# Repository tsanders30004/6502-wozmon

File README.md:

# 6502 PCB Computer

## INTRODUCTION
- I was in highschool in the eighties when the *home computer revolution* introduced the world to computers running the MOS6502 and Z80 microprocessors.
- My first computer was an Atari 400 which used a 6502.
- When I added two numbers together in BASIC for the first time on that computer, I was hooked.   To this day, I am fascinated with computers.
- I couldn't help feeling nostalgic when I stumbled upon Ben Eater's excellent https://eater.net/6502 webpage, in which he describes how to build a 6502 computer on a breadboard.
- I quickly found out how difficult working with breadboards can be RE: unreliable connections, etc.  One loose wire was all it took to make the computer unusable.
- I therefore abandoned the breadboard altogether and instead decided to build a PCB.
- I had no idea how to do this; I could not even solder.  But I figured all of that out, and eventually I had a PCB that can run *HELLO WORLD* and *WOZMON*.
- This repository has all of the files necessary to build that PCB.

## PCB DESCRIPTION

|General Information||
|-|-|
|Microprocessor|WDC 65c02|
|I/O|65c22|
|UART|65c51|
|Clock|1MHz|
|ROM|32KB|
|RAM|32KB|
|Display|40x2 character LCD|
|Baud Rate|19200 8N1|

The upper left corner of the PCB has ports for +5V (barrel connector) and an RS-232 nine-pin serial cable.  
PWR and CLK LED's will illuminate when power and a clock signal (from the onboard 1MHz clock) are present, respectively.
The PCB can be reset via the RESET button directly below the RS-232 port.  The RESET LED will illuminate when the RESET button is pressed.

A column of output header pins is positioned immediately to the left of the LCD.  These output pins were primarily used for testing.  The top four pins are for GND.  (I used then when connecting the ground lead of an oscilloscope to the PCB.)  The bottom four pins are TxD, MAX232 pin 12, RESET*, and the CLOCK signal.  You can leave these pins unconnected if you don't want to use them.

## SOFTWARE 

|Filename|Description|
|-|-|
|software/hello/hello.s|'HELLO WORLD 6502' Assembly Code|
|software/hello/hello.out|'HELLO WORLD 6502' ROM file
|software/wozmon/wozmin.s|WOZMON Assembly Code|
|software/wozmon/wozmin.bin|WOZMON ROM file|

The computer *does not run the version of Microsoft BASIC* that Ben describes on his channel.  I have not figured (yet?) why that is so.  But it does run an alternate version of BASIC I found on Github.  See https://github.com/Fifty1Ford/BeEhBasic for more information.

## KICAD FILES

I used KiCad 6 to design the PCB.  
|Filename|Description|
|-|-|
|6502_wozmon.kicad_pro|KiCad 6 Project File|
|6502_wozmon.kicad_sch|KiCad 6 Schematic|
|6502_wozmon.kicad_pcb|KiCad 6 PCB File|
|6502_wozmon.csv|Bill of Materials|
|barrel_jack.pdf|Barrel Jack Power Connector|
|schematic.pdf|Schematic|
|photos/*.png|Photos|
|gerber/*|Gerber Files|

## CLOSING COMMENTS
- I am a hobbyist.  There are no doubt many ways to improve this design.  Feel free to do so! 
- I use a ZIF socket for the ROM chip to make it easier to remove.

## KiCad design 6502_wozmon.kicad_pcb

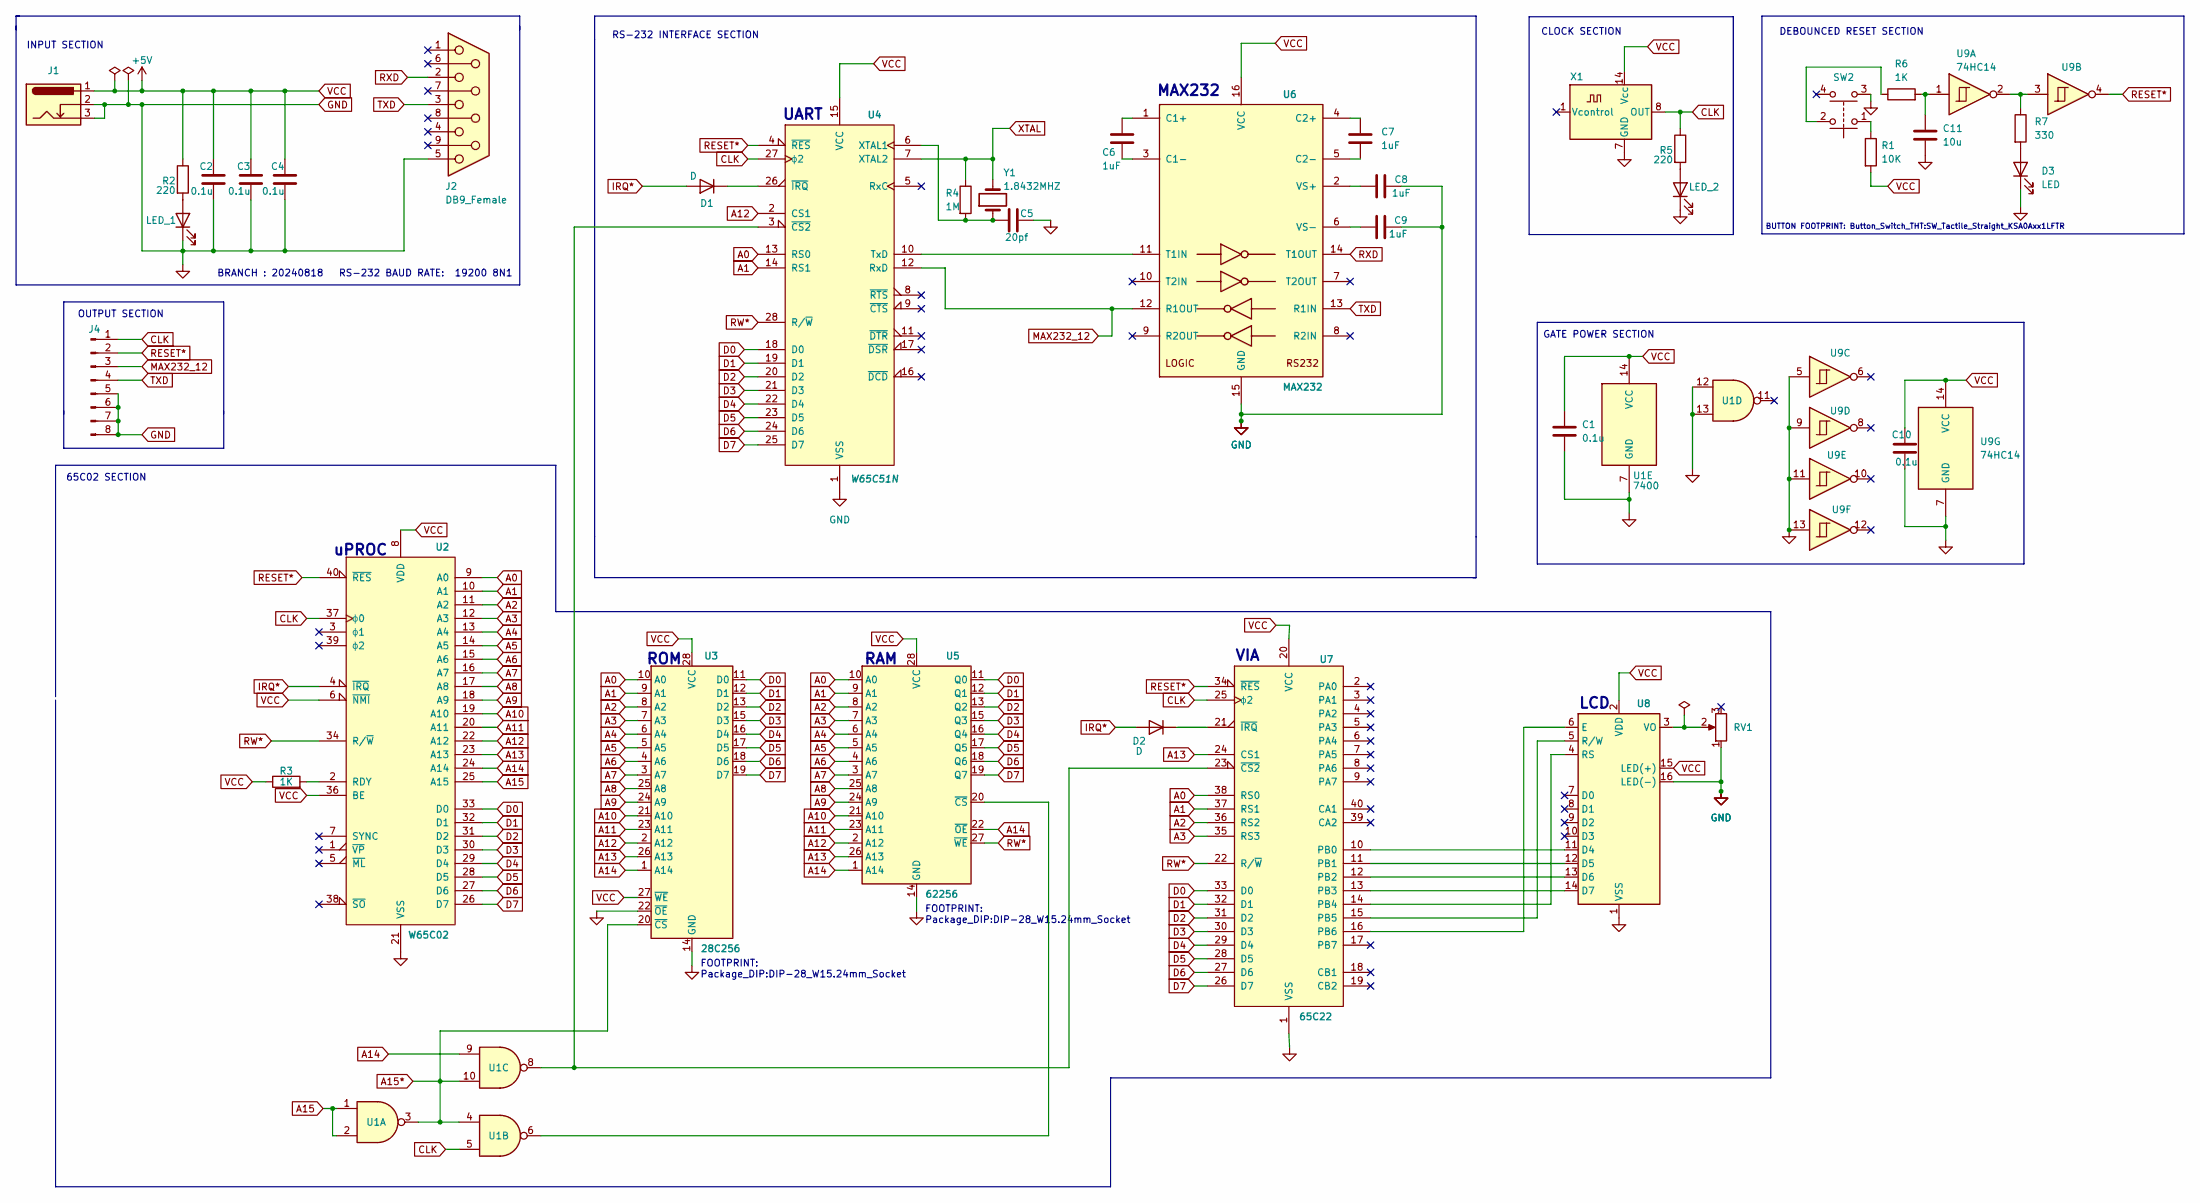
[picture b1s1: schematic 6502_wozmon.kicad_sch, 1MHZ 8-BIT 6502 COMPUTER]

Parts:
C1, C2, C3, C4, C10: 0.1u; C_Disc_D5.0mm_W2.5mm_P5.00mm
C5: 20pf; C_Disc_D5.0mm_W2.5mm_P5.00mm
C6, C7, C8, C9: 1uF; C_Disc_D5.0mm_W2.5mm_P5.00mm
C11: 10u; C_Disc_D5.0mm_W2.5mm_P5.00mm
D1, D2: D; D_A-405_P10.16mm_Horizontal
D3: LED; LED_D5.0mm
J1: Barrel_Jack_Switch_Pin3Ring; BarrelJack_Horizontal
J2: DB9_Female; DSUB-9_Female_Horizontal_P2.77x2.84mm_EdgePinOffset9.90mm_H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
J4: Conn_01x08_Male; PinHeader_1x08_P2.54mm_Vertical
LED_1, LED_2: LED; LED_D5.0mm
R1: 10K; R_Axial_DIN0207_L6.3mm_D2.5mm_P10.16mm_Horizontal
R2, R5: 220; R_Axial_DIN0207_L6.3mm_D2.5mm_P10.16mm_Horizontal
R3, R6: 1K; R_Axial_DIN0207_L6.3mm_D2.5mm_P10.16mm_Horizontal
R4: 1M; R_Axial_DIN0207_L6.3mm_D2.5mm_P10.16mm_Horizontal
R7: 330; R_Axial_DIN0207_L6.3mm_D2.5mm_P10.16mm_Horizontal
RV1: R_Potentiometer; Potentiometer_Bourns_3266Y_Vertical
SW2: SW_Push_Dual; SW_Tactile_Straight_KSA0Axx1LFTR
U1: 7400; DIP-14_W7.62mm_Socket
U2: W65C02; DIP-40_W15.24mm_Socket
U3: 28C256; DIP-28_W15.24mm_Socket
U4: W65C51N; DIP-28_W15.24mm_Socket
U5: 62256; DIP_Socket-28_W11.9_W12.7_W15.24_W17.78_W18.5_3M_228-1277-0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
U6: MAX232; DIP-16_W7.62mm_Socket
U7: 65C22; DIP-40_W15.24mm_Socket
U8: WC1602A
U9: 74HC14; DIP-14_W7.62mm_Socket
X1: GTXO-S14V; Oscillator_DIP-14
Y1: 1.8432MHZ; Crystal_HC18-U_Vertical

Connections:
A0: U2.9 (A0), U3.10 (A0), U4.13 (RS0), U5.10 (A0), U7.38 (RS0)
A1: U2.10 (A1), U3.9 (A1), U4.14 (RS1), U5.9 (A1), U7.37 (RS1)
A2: U2.11 (A2), U3.8 (A2), U5.8 (A2), U7.36 (RS2)
A3: U2.12 (A3), U3.7 (A3), U5.7 (A3), U7.35 (RS3)
A4: U2.13 (A4), U3.6 (A4), U5.6 (A4)
A5: U2.14 (A5), U3.5 (A5), U5.5 (A5)
A6: U2.15 (A6), U3.4 (A6), U5.4 (A6)
A7: U2.16 (A7), U3.3 (A7), U5.3 (A7)
A8: U2.17 (A8), U3.25 (A8), U5.25 (A8)
A9: U2.18 (A9), U3.24 (A9), U5.24 (A9)
A10: U2.19 (A10), U3.21 (A10), U5.21 (A10)
A11: U2.20 (A11), U3.23 (A11), U5.23 (A11)
A12: U2.22 (A12), U3.2 (A12), U4.2 (CS1), U5.2 (A12)
A13: U2.23 (A13), U3.26 (A13), U5.26 (A13), U7.24 (CS1)
A14: U1.9, U2.24 (A14), U3.1 (A14), U5.1 (A14), U5.22 (~OE)
A15: U1.1, U1.2, U2.25 (A15)
A15*: U1.3, U1.4, U1.10, U3.20 (~CS)
CLK: J4.1, R5.1, U1.5, U2.37 (ϕ0), U4.27 (ϕ2), U7.25 (ϕ2), X1.8 (OUT)
D0: U2.33 (D0), U3.11 (D0), U4.18 (D0), U5.11 (Q0), U7.33 (D0)
D1: U2.32 (D1), U3.12 (D1), U4.19 (D1), U5.12 (Q1), U7.32 (D1)
D2: U2.31 (D2), U3.13 (D2), U4.20 (D2), U5.13 (Q2), U7.31 (D2)
D3: U2.30 (D3), U3.15 (D3), U4.21 (D3), U5.15 (Q3), U7.30 (D3)
D4: U2.29 (D4), U3.16 (D4), U4.22 (D4), U5.16 (Q4), U7.29 (D4)
D5: U2.28 (D5), U3.17 (D5), U4.23 (D5), U5.17 (Q5), U7.28 (D5)
D6: U2.27 (D6), U3.18 (D6), U4.24 (D6), U5.18 (Q6), U7.27 (D6)
D7: U2.26 (D7), U3.19 (D7), U4.25 (D7), U5.19 (Q7), U7.26 (D7)
GND: C1.2, C2.2, C3.2, C4.2, C5.2, C8.1, C9.2, C10.2, C11.2, D3.1 (K), J1.2, J1.3, J2.5, J4.5, J4.6, J4.7, J4.8, LED_1.1 (K), LED_2.1 (K), RV1.1, SW2.3, U1.7 (GND), U1.12, U1.13, U2.21 (VSS), U3.14 (GND), U3.22 (~OE), U4.1 (VSS), U5.14 (GND), U6.15 (GND), U7.1 (VSS), U8.1 (VSS), U8.16 (LED(-)), U9.5, U9.7 (GND), U9.9, U9.11, U9.13, X1.7 (GND)
IRQ*: D1.2 (A), D2.2 (A), U2.4 (~IRQ)
MAX232_12: J4.3, U4.12 (RxD), U6.12 (R1OUT)
unnamed: C5.1, R4.2, U4.6 (XTAL1), Y1.1
unnamed: C6.1, U6.1 (C1+)
unnamed: C6.2, U6.3 (C1-)
unnamed: C7.1, U6.4 (C2+)
unnamed: C7.2, U6.5 (C2-)
unnamed: C8.2, U6.2 (VS+)
unnamed: C9.1, U6.6 (VS-)
unnamed: C11.1, R6.2, U9.1
unnamed: D1.1 (K), U4.26 (~IRQ)
unnamed: D2.1 (K), U7.21 (~IRQ)
unnamed: D3.2 (A), R7.2
unnamed: LED_1.2 (A), R2.2
unnamed: LED_2.2 (A), R5.2
unnamed: R1.1, SW2.1
unnamed: R3.2, U2.2 (RDY)
unnamed: R6.1, SW2.2
unnamed: R7.1, U9.2, U9.3
unnamed: RV1.2, U8.3 (VO)
unnamed: U1.6, U5.20 (~CS)
unnamed: U1.8, U4.3 (~CS2), U7.23 (~CS2)
unnamed: U4.10 (TxD), U6.11 (T1IN)
unnamed: U7.10 (PB0), U8.11 (D4)
unnamed: U7.11 (PB1), U8.12 (D5)
unnamed: U7.12 (PB2), U8.13 (D6)
unnamed: U7.13 (PB3), U8.14 (D7)
unnamed: U7.14 (PB4), U8.4 (RS)
unnamed: U7.15 (PB5), U8.5 (R/W)
unnamed: U7.16 (PB6), U8.6 (E)
RESET*: J4.2, U2.40 (~RES), U4.4 (~RES), U7.34 (~RES), U9.4
RW*: U2.34 (R/~W), U4.28 (R/~W), U5.27 (~WE), U7.22 (R/~W)
RXD: J2.2, U6.14 (T1OUT)
TXD: J2.3, J4.4, U6.13 (R1IN)
VCC: C1.1, C2.1, C3.1, C4.1, C10.1, J1.1, R1.2, R2.1, R3.1, U1.14 (VCC), U2.6 (~NMI), U2.8 (VDD), U2.36 (BE), U3.27 (~WE), U3.28 (VCC), U4.15 (VCC), U5.28 (VCC), U6.16 (VCC), U7.20 (VCC), U8.2 (VDD), U8.15 (LED(+)), U9.14 (VCC), X1.14 (Vcc)
XTAL: R4.1, U4.7 (XTAL2), Y1.2

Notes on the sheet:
FOOTPRINT: Package_DIP:DIP-28_W15.24mm_Socket
UART
OUTPUT SECTION
CLOCK SECTION
65C02 SECTION
INPUT SECTION
MAX232
BRANCH : 20240818
GATE POWER SECTION
ROM
BUTTON FOOTPRINT: Button_Switch_THT:SW_Tactile_Straight_KSA0Axx1LFTR
RAM
uPROC
DEBOUNCED RESET SECTION
RS-232 INTERFACE SECTION
LCD
VIA
RS-232 BAUD RATE: 19200 8N1

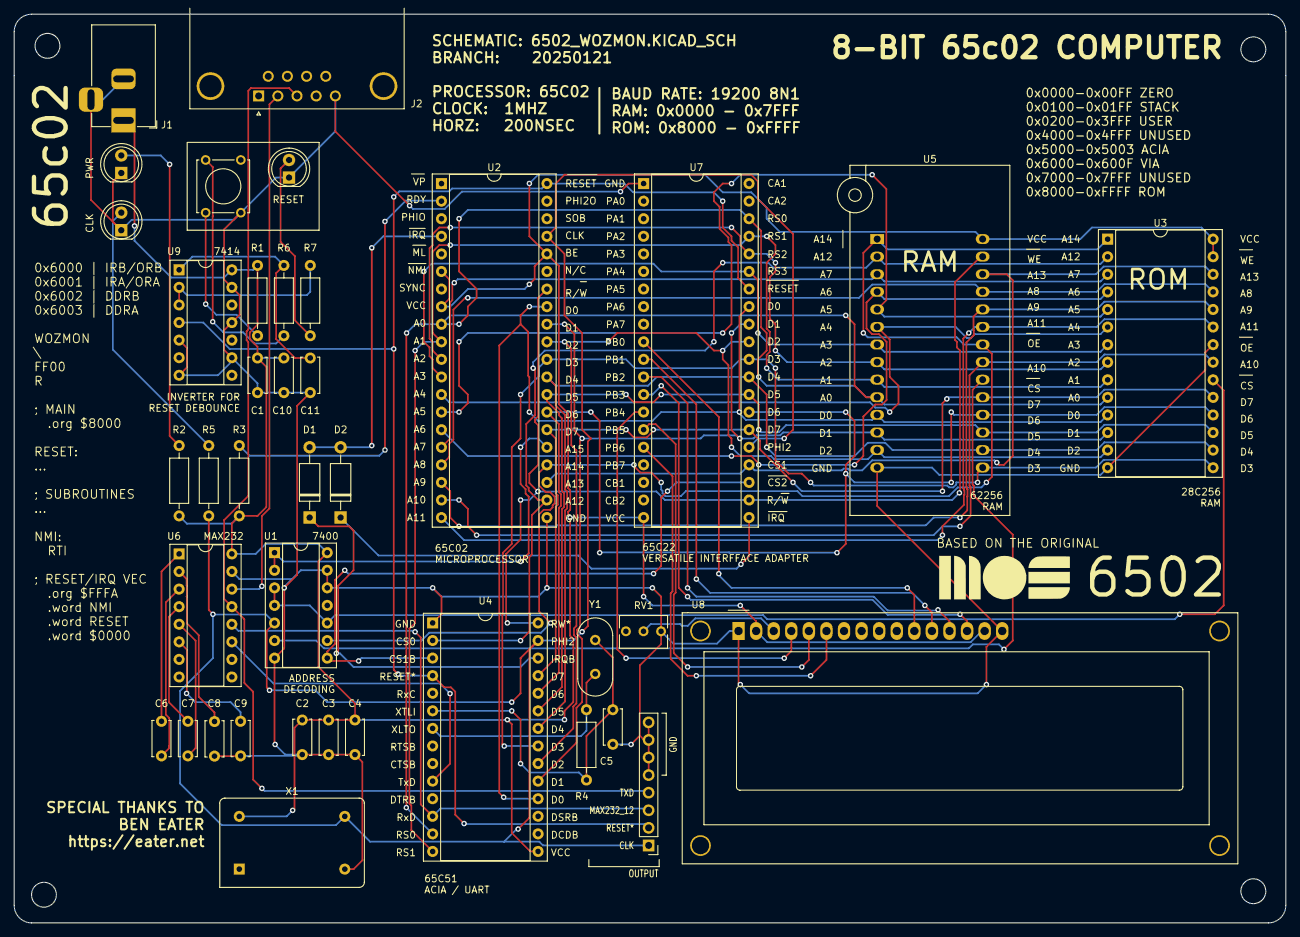
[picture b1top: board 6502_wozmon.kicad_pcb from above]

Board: 2 copper layers, 183.7 x 131.3 mm, 39 parts (0 on the bottom side), 63 nets.

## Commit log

2024-07-20 First commit.
2024-07-20 schematic updated to include debounced reset section; added barrel connector.
2024-07-20 updated .gitignore.
2024-07-21 increment
2024-07-21 1. Updated Files A. The pin headers being used as a switch were replaced with a proper button switch and footprint. a. The following were updated: 1. 6502_wozmon.kicad_pcb 2. 6502_wozmon.kicad_prl 2.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
2024-08-04 Added gerber files.
2024-09-02 Added README.md, photos, and sotware files.
